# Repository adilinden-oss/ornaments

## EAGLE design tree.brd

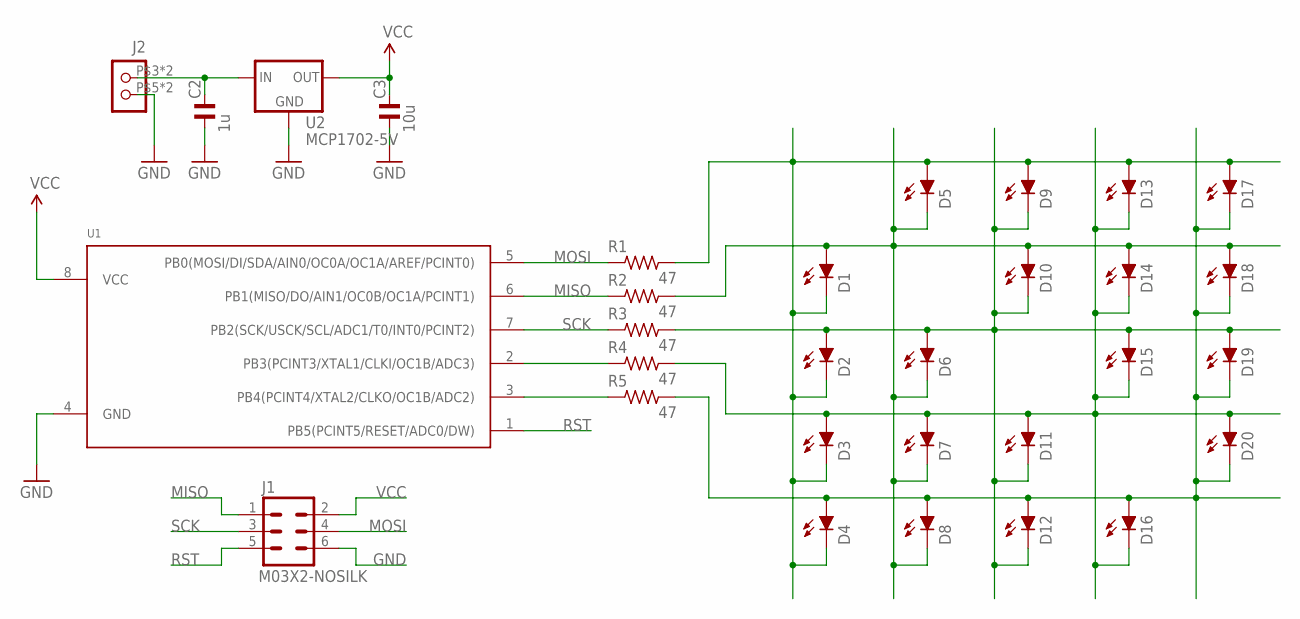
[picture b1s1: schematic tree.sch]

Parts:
C2: 1u; C0805NOSILK
C3: 10u; C0805NOSILK
D1, D2, D3, D4, D5, D6, D7, D8, D9, D10, D11, D12, D13, D14, D15, D16, D17, D18, D19, D20: LEDCHIP-LED0805NOSILK; CHIP-LED0805NOSILK
J1: M03X2-NOSILK; 2X03_LOCK_NOSILK
J2: CON_TERMINAL_HOLES; TERMINAL_2P_4H
R1, R2, R3, R4, R5: 47; R0805NOSILK
U1: ATTINY5-20SU-NOSILK; SOP8-8S2-NOSILK
U2: MCP1702-5V; SOT23_NOSILK

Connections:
GND: C2.1, C3.1, J1.6, J2.P$5 (2), J2.P$6 (2), U1.4 (GND), U2.1 (GND)
MISO: J1.1, R2.1, U1.6 (PB1(MISO/DO/AIN1/OC0B/OC1A/PCINT1))
MOSI: J1.4, R1.1, U1.5 (PB0(MOSI/DI/SDA/AIN0/OC0A/OC1A/AREF/PCI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)
unnamed: C2.2, J2.P$3 (1), J2.P$4 (1), U2.3 (IN)
unnamed: R4.1, U1.2 (PB3(PCINT3/XTAL1/CLKI/OC1B/ADC3))
unnamed: R5.1, U1.3 (PB4(PCINT4/XTAL2/CLKO/OC1B/ADC2))
unnamed: D2.A, D6.A, D9.C, D10.C, D11.C, D12.C, D15.A, D19.A, R3.2
unnamed: D1.A, D5.C, D6.C, D7.C, D8.C, D10.A, D14.A, D18.A, R2.2
unnamed: D1.C, D2.C, D3.C, D4.C, D5.A, D9.A, D13.A, D17.A, R1.2
unnamed: D3.A, D7.A, D11.A, D13.C, D14.C, D15.C, D16.C, D20.A, R4.2
unnamed: D4.A, D8.A, D12.A, D16.A, D17.C, D18.C, D19.C, D20.C, R5.2
RST: J1.5, U1.1 (PB5(PCINT5/RESET/ADC0/DW))
SCK: J1.3, R3.1, U1.7 (PB2(SCK/USCK/SCL/ADC1/T0/INT0/PCINT2))
VCC: C3.2, J1.2, U1.8 (VCC), U2.2 (OUT)

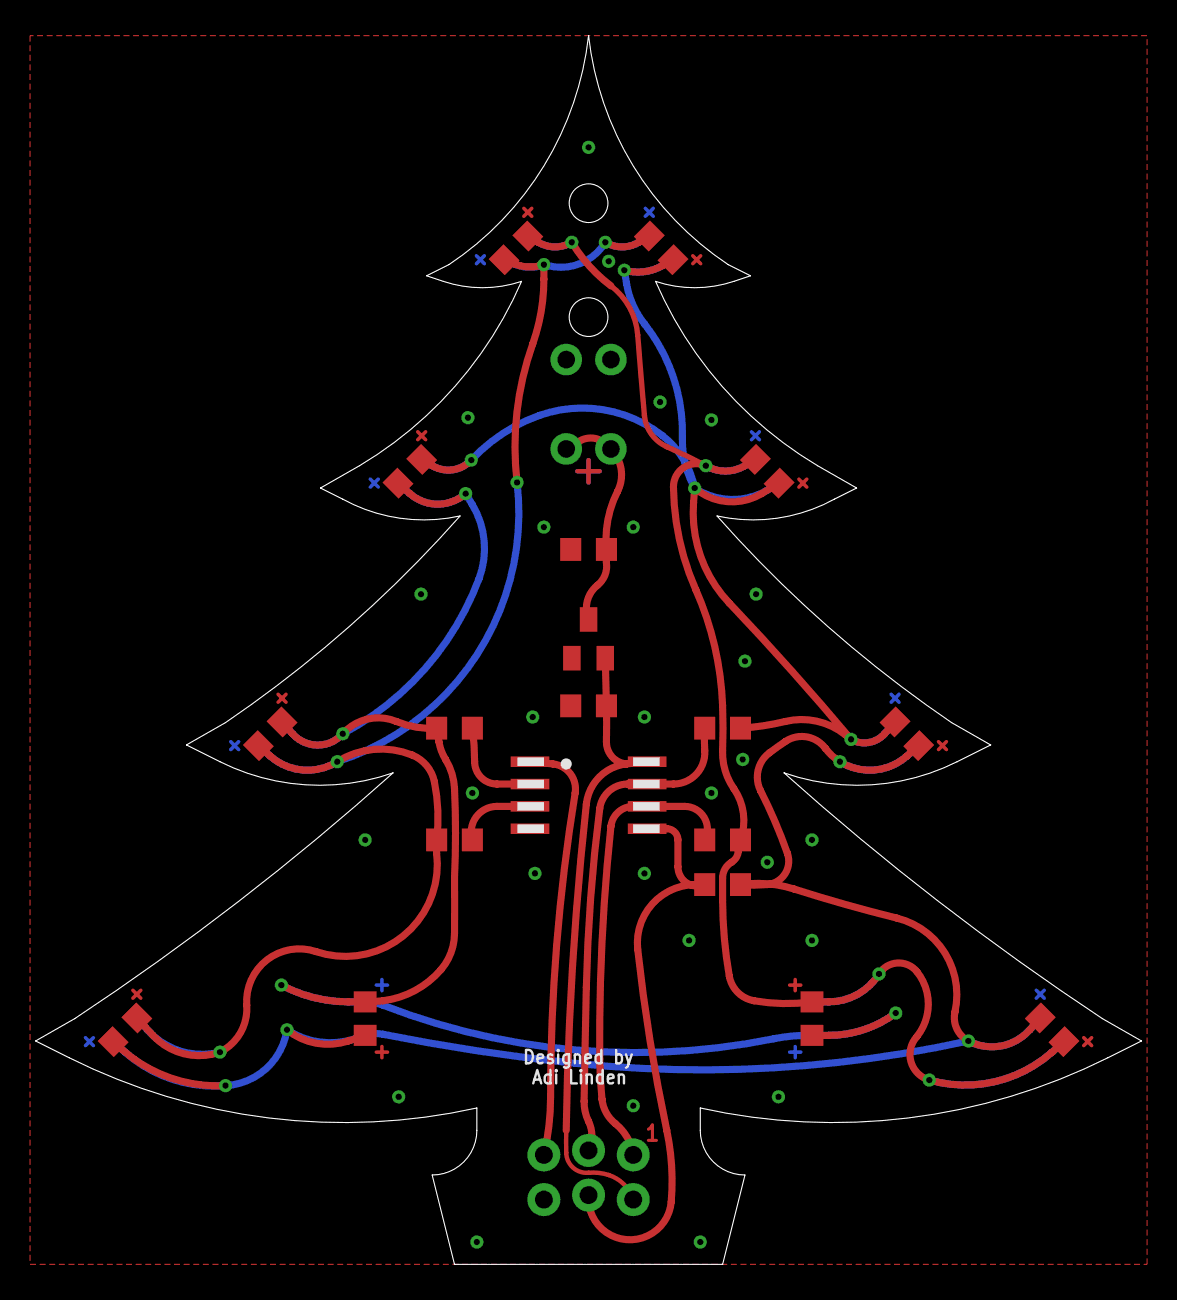
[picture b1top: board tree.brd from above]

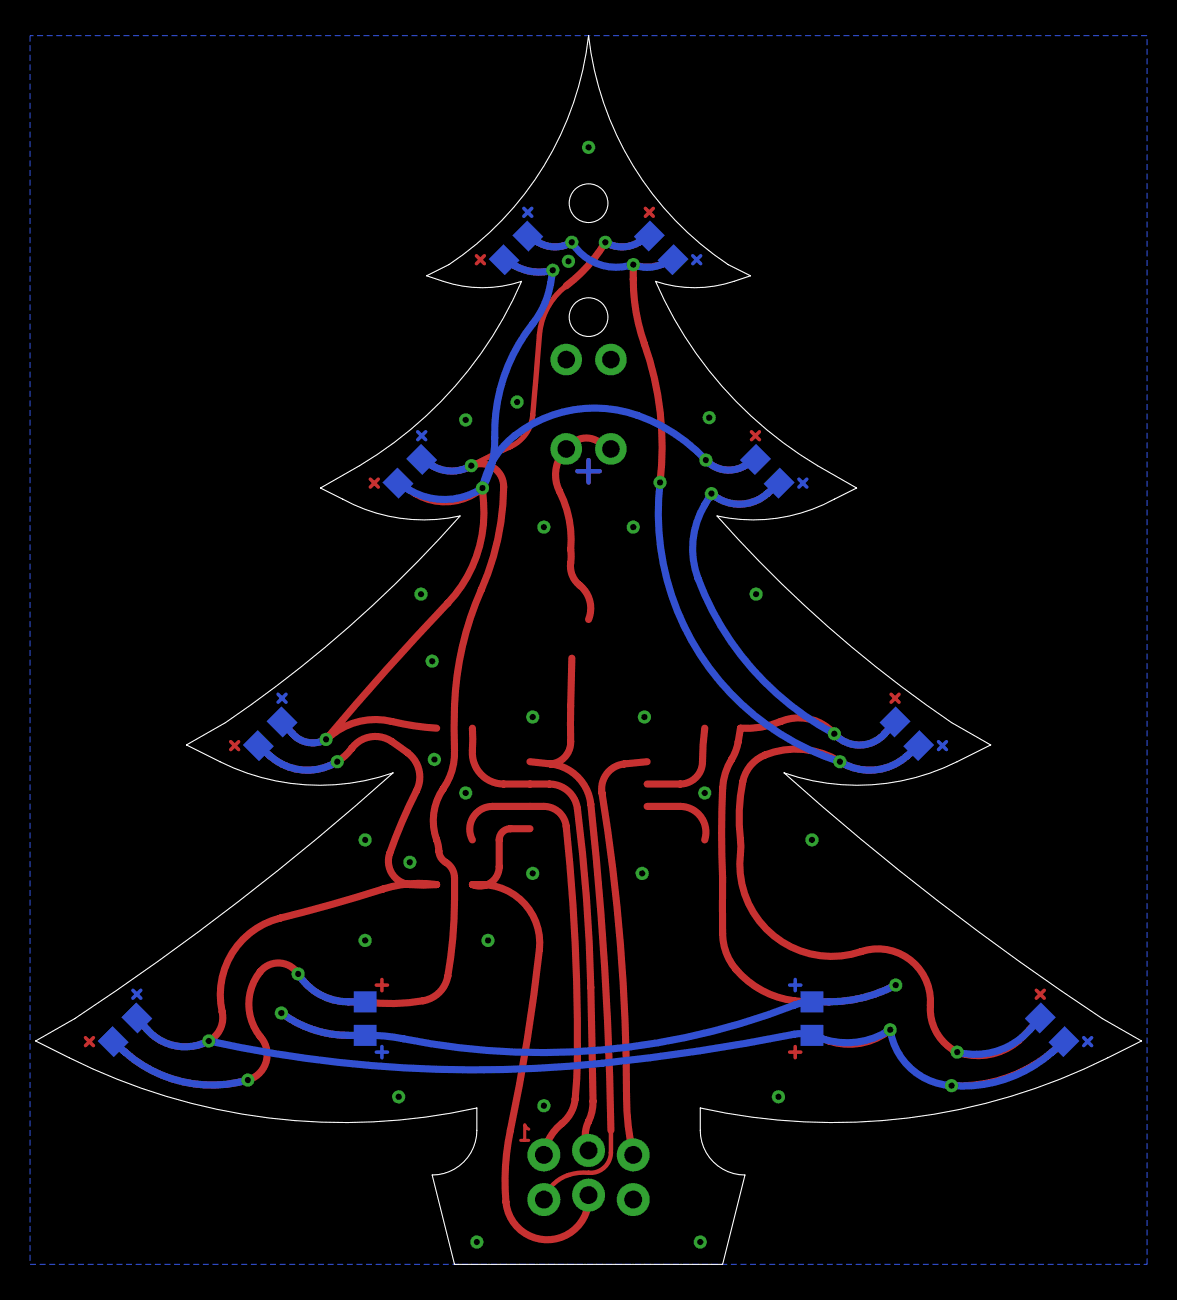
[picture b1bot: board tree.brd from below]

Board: 2 copper layers, 62.9 x 69.8 mm, 31 parts (10 on the bottom side), 14 nets.

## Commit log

2016-11-15 Added snowflake.
2016-11-16 Placed LED more logical.
2016-11-17 Ground floods, vias, slights adjustmens to facilitate better flooding.
2016-11-17 Unified name font size and width. Changed names to tDocu and bDocu layers to keep off silk.
2016-11-17 Fixed ATTINY no silk.
2016-11-17 Fixes.
2016-11-17 Removed first version of snowflake.
2016-11-17 Renamed to make it just a single version.
2016-11-17 It's a star, not a snowflake.
2016-11-17 Added tree.
2016-11-17 Removed redundant cap.
2016-11-17 Added 'Designed by...'.
2016-11-17 Created png. Added values to schematic.
2016-11-17 Created gerber for FusionPCB order.

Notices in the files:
parts and their libraries:
SparkFun-Aesthetics: Licensing: Creative Commons ShareAlike 4.0 International - https://creativecommons.org/licenses/by-sa/4.0
